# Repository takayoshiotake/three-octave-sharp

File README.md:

# Three Octave \#

[![CC BY-SA 4.0][cc-by-sa-shield]][cc-by-sa]

A 38-key (3-octave + 1) keyboard. Powered by [Vial](https://get.vial.today/) firmware.

This keyboard is based on a 60% column staggered keyboard like the HHKB, which omits the number and symbol keys to reduce the number of keys to 38.

## Layout

v0.3.0

**Layer 0**:

MEMO: I couldn't figure out how to map keys to `fn` on macOS using Vial, so I am using Karabiner-Elements, a macOS app, to modify `right_control` to `fn`.

**Layer 1, 2**: arrows, symbols

**Layer 3, 4**: nums, symbols

**Layer 5**: fn

**RAW data for Keyboard Layout Editor v0.15:**

📄 [keyboard-layout.rawdata.json](layout/keyboard-layout.rawdata.json)

```json
[{a:1},"LT 2\nEsc",{a:7},"Q","W","E","R","T","Y","U","I","O","P","Bksp"],
[{a:1,w:1.25},"LT 1\nTab",{a:7},"A","S","D","F","G","H","J","K","L",{a:1,w:1.75},"LT 4\nEnter"],
[{a:7,w:1.75},"LShift","Z","X","C","V","B","N","M","MO(5)",{w:2.25},"MO(3)"],
[{x:0.75,w:1.25},"LCtrl",{a:1,w:1.25},"LGui_T\n英数",{a:7,w:6},"6u",{a:1},"RAlt_T\nかな",{a:7},"RCtrl"],
```

- 🔗 [Keyboard Layout Editor](http://www.keyboard-layout-editor.com/)

## BOM

| Material | QTY | Note |
|-|-:|-|
| Three Octave Sharp PCBA | 1 | |
| Three Octave Sharp Case | 1 | |
| B-0204 | 4 | Screw M2 L4, Hirosugi |
| SIS-2039-05 | 4 | Washer d2 D3.9 t0.5, Hirosugi |
| LUW-0204-075 | 4 | Washer d2.2 D4 t0.075, Hirosugi |

### Three Octave Sharp PCBA

| Material | Symbol | QTY | Note |
|-|-|-:|-|
| Three Octave Sharp PCB | - | 1 | |
| 30pF 402 | C1, C2 | 2 | C1570 |
| 1uF 402 | C3, C4 | 2 | C52923 |
| 100nF 402 | C5-C14 | 10 | C307331 |
| 10uF 402 | C15, C16 | 2 | C15525 |
| HRO_TYPE-C-31-M-12 | J1 | 1 | C165948; USB Type-C Connector, Korean Hroparts Elec |
| 10KΩ 0402 | R1, R3 | 2 | C25744 |
| 1KΩ 0402 | R2, R4 | 2 | C11702 |
| 27Ω 0402 | R5, R6 | 2 | C352446 |
| 5.1KΩ 0402 | R7, R8 | 2 | C25905 |
| Hot_Swap_Socket_CPG151101S11 | SW1-SW38 | 38 | C5156480; How Swap Socket, Kailh |
| SKRPANE010 | SW_B1, SW_R1 | 2 | C470426; Tactile Switch, ALPS ALPINE |
| RP2040 | U1 | 1 | C2040; MCU, Raspberry Pi |
| W25Q64JVXGIQ | U2 | 1 | C2940195, 64M-bit Serial Flash, Winbond Electronics |
| AP2112K-3.3TRG1 | U3 | 1 | C51118, 3.3V Linear Voltage Regulators |
| X322512MSB4SI | Y1 | 1 | C9002, 12MHz 20pF Crystal Resonator, SMD-3225, Yangxing Tech |

📁 [production_data (for JLCPCB at 2024-01-25)](electronics/Three_Octave_Sharp/production/Three_Octave_Sharp_1.0.0_2024-01-25_19-34-58)

### Three Octave Sharp Case

WIP

## Schematic and PCB

📄 [Three_Octave_Sharp.kicad_sch](electronics/Three_Octave_Sharp/Three_Octave_Sharp.kicad_sch) (v1.0.0)

📄 [Three_Octave_Sharp.kicad_pcb](electronics/Three_Octave_Sharp/Three_Octave_Sharp.kicad_pcb) (v1.0.1)

### Key-matrix

|    | C0    | C1   | C2    | C3 | C4 | C5 | C6 | C7 | C8 | C9    | C10    | C11 |
|----|-------|------|-------|----|----|----|----|----|----|-------|--------|-----|
| R0 | Esc   | Q    | W     | E  | R  | T  | Y  | U  | I  | O     | P      | BS  |
| R1 | Tab   | A    | S     | D  | F  | G  | H  | J  | K  | L     | Return |     |
| R2 | Shift | Z    | X     | C  | V  | B  | N  | M  | ,  | Shift | Opt    | Fn  | 
| R3 | Ctrl  | Cmd  | Space |    |    |    |    |    |    |       |        |     |

## Mechanics

The case also functions as a plate.

- 📄 [Three-Octave-Sharp-Case.FCStd](mechanics/Three-Octave-Sharp-Case.FCStd) (v1.0.3)
    - 📄 [Three-Octave-Sharp-Case-Top.step](mechanics/Three-Octave-Sharp-Case-Top.step)
    - 📄 [Three-Octave-Sharp-Case-Bottom.step](Three-Octave-Sharp-Case-Bottom.step)

<div style="display: grid; gap: 1px; grid-template: 'a0 a0 a0 a0' 'a2t a2t a2b a2b' 'a5t a5t a5b a5b' 'a1 a3 a4 a6';">

</div>

## Firmware

### Vial

- Built UF2
    - 📄 [takayoshiotake_three_octave_sharp_vial_20240407.uf2](vial-bin/takayoshiotake_three_octave_sharp_vial_20240407.uf2)
- Code
    - 🔗 <https://github.com/vial-kb/vial-qmk/tree/vial/keyboards/takayoshiotake/three_octave_sharp>
    - 🔗 <https://github.com/vial-kb/vial-qmk/tree/bbaed80505cf4ceaeb51d1e5fe79b23b22acf1a6>

See [vial-porting](vial-porting) for more details.

## License

This work is licensed under a
[Creative Commons Attribution-ShareAlike 4.0 International License][cc-by-sa].

[![CC BY-SA 4.0][cc-by-sa-image]][cc-by-sa]

[cc-by-sa]: http://creativecommons.org/licenses/by-sa/4.0/
[cc-by-sa-image]: https://licensebuttons.net/l/by-sa/4.0/88x31.png
[cc-by-sa-shield]: https://img.shields.io/badge/license-CC%20BY--SA%204.0-lightgrey.svg

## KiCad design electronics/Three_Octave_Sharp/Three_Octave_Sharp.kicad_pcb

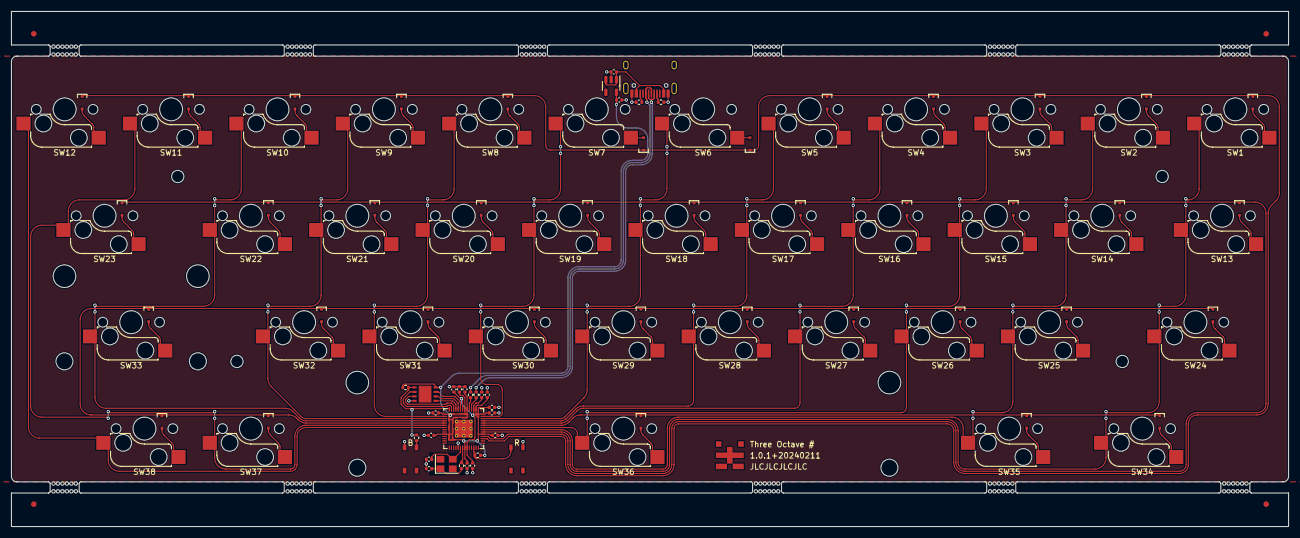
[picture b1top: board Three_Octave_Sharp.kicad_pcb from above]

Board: 2 copper layers, 228.6 x 92.2 mm, 107 parts (0 on the bottom side), 75 nets.

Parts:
C1, C2: 30pF; C_0402_1005Metric
C3, C4: 1uF; C_0402_1005Metric
C5, C6, C7, C8, C9, C10, C11, C12, C13, C14: 0.1uF; C_0402_1005Metric
C15, C16: 10uF; C_0402_1005Metric
D1, D2, D3, D4, D5, D6, D7, D8, D9, D10, D11, D12, D13, D14, D15, D16, D17, D18, D19, D20, D21, D22, D23, D24, D25, D26, D27, D28, D29, D30, D31, D32, D33, D34, D35, D36, D37, D38: 1N4148WS; D_SOD-323F
J1: HRO_TYPE-C-31-M-12
R1, R3: 10K; R_0402_1005Metric
R2, R4: 1K; R_0402_1005Metric
R5, R6: 27; R_0402_1005Metric
R7, R8: 5.1K; R_0402_1005Metric
SW1: Key Tab; Hot_Swap_Socket_CPG151101S11
SW2: Key Q; Hot_Swap_Socket_CPG151101S11
SW3: Key W; Hot_Swap_Socket_CPG151101S11
SW4: Key E; Hot_Swap_Socket_CPG151101S11
SW5: Key R; Hot_Swap_Socket_CPG151101S11
SW6: Key T; Hot_Swap_Socket_CPG151101S11
SW7: Key Y; Hot_Swap_Socket_CPG151101S11
SW8: Key U; Hot_Swap_Socket_CPG151101S11
SW9: Key I; Hot_Swap_Socket_CPG151101S11
SW10: Key O; Hot_Swap_Socket_CPG151101S11
SW11: Key P; Hot_Swap_Socket_CPG151101S11
SW12: Key BS; Hot_Swap_Socket_CPG151101S11
SW13: Key Caps; Hot_Swap_Socket_CPG151101S11
SW14: Key A; Hot_Swap_Socket_CPG151101S11
SW15: Key S; Hot_Swap_Socket_CPG151101S11
SW16: Key D; Hot_Swap_Socket_CPG151101S11
SW17: Key F; Hot_Swap_Socket_CPG151101S11
SW18: Key G; Hot_Swap_Socket_CPG151101S11
SW19: Key H; Hot_Swap_Socket_CPG151101S11
SW20: Key J; Hot_Swap_Socket_CPG151101S11
SW21: Key K; Hot_Swap_Socket_CPG151101S11
SW22: Key L; Hot_Swap_Socket_CPG151101S11
SW23: Key Return; Hot_Swap_Socket_CPG151101S11
SW24, SW33: Key Shift; Hot_Swap_Socket_CPG151101S11
SW25: Key Z; Hot_Swap_Socket_CPG151101S11
SW26: Key X; Hot_Swap_Socket_CPG151101S11
SW27: Key C; Hot_Swap_Socket_CPG151101S11
SW28: Key V; Hot_Swap_Socket_CPG151101S11
SW29: Key B; Hot_Swap_Socket_CPG151101S11
SW30: Key N; Hot_Swap_Socket_CPG151101S11
SW31: Key M; Hot_Swap_Socket_CPG151101S11
SW32: Key ,; Hot_Swap_Socket_CPG151101S11
SW34: Key Ctrl; Hot_Swap_Socket_CPG151101S11
SW35: Key Cmd; Hot_Swap_Socket_CPG151101S11
SW36: Key Space; Hot_Swap_Socket_CPG151101S11
SW37: Key Opt; Hot_Swap_Socket_CPG151101S11
SW38: Key Fn; Hot_Swap_Socket_CPG151101S11
SW_B1: Alps_Alpine_SKRP; Tactile_Switch_SKRP_Series
SW_R1: Alps_Alpine_SKRP; Tactile_Switch_SKRP_Series
U1: Raspberry_Pi_RP2040; RP2040_QFN-56
U2: W25Q64JVXGIQ; XSON-8-EP_4x4mm
U3: AP2112K-3.3; SOT-23-5
Y1: 12MHz; Crystal_SMD_3225-4Pin_3.2x2.5mm

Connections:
+1V1: C4.1, C13.1, C14.1, U1.23 (DVDD), U1.45 (VREG_VOUT), U1.50 (DVDD)
+3V3: C3.1, C5.1, C6.1, C7.1, C8.1, C9.1, C10.1, C11.1, C12.1, C16.1, R1.1, R3.1, U1.1 (IOVDD), U1.10 (IOVDD), U1.22 (IOVDD), U1.33 (IOVDD), U1.42 (IOVDD), U1.43 (ADC_AVDD), U1.44 (VREG_VIN), U1.48 (USB_VDD), U1.49 (IOVDD), U2.8 (VCC), U3.5 (VOUT)
+5V: C15.1, J1.A4/B9 (VBUS), J1.A9/B4 (VBUS), U3.1 (VIN), U3.3 (EN)
COL0: SW1.2, SW13.2, SW24.2, SW34.2, U1.34 (GPIO22)
COL1: SW2.2, SW14.2, SW25.2, SW35.2, U1.35 (GPIO23)
COL2: SW3.2, SW15.2, SW26.2, SW36.2, U1.36 (GPIO24)
COL3: SW4.2, SW16.2, SW27.2, U1.38 (GPIO26/ADC0)
COL4: SW5.2, SW17.2, SW28.2, U1.39 (GPIO27/ADC1)
COL5: SW6.2, SW18.2, SW29.2, U1.40 (GPIO28/ADC2)
COL6: SW7.2, SW19.2, SW30.2, U1.41 (GPIO29/ADC3)
COL7: SW8.2, SW20.2, SW31.2, U1.2 (GPIO0)
COL8: SW9.2, SW21.2, SW32.2, U1.3 (GPIO1)
COL9: SW10.2, SW22.2, SW33.2, U1.4 (GPIO2)
COL10: SW11.2, SW23.2, SW37.2, U1.6 (GPIO4)
COL11: SW12.2, SW38.2, U1.7 (GPIO5)
D+: R5.1, U1.47 (USB_DP)
D-: R6.1, U1.46 (USB_DM)
GND: C1.2, C2.2, C3.2, C4.2, C5.2, C6.2, C7.2, C8.2, C9.2, C10.2, C11.2, C12.2, C13.2, C14.2, C15.2, C16.2, J1.A1/B12 (GND), J1.A12/B1 (GND), R7.2, R8.2, SW_B1.3, SW_R1.1, U1.19 (TESTEN), U1.57 (GND), U2.4 (GND), U3.2 (GND)
unnamed: C2.1, R2.2, Y1.1
unnamed: D1.2 (A), SW1.1
unnamed: D2.2 (A), SW2.1
unnamed: D3.2 (A), SW3.1
unnamed: D4.2 (A), SW4.1
unnamed: D5.2 (A), SW5.1
unnamed: D6.2 (A), SW6.1
unnamed: D7.2 (A), SW7.1
unnamed: D8.2 (A), SW8.1
unnamed: D9.2 (A), SW9.1
unnamed: D10.2 (A), SW10.1
unnamed: D11.2 (A), SW11.1
unnamed: D12.2 (A), SW12.1
unnamed: D13.2 (A), SW13.1
unnamed: D14.2 (A), SW14.1
unnamed: D15.2 (A), SW15.1
unnamed: D16.2 (A), SW16.1
unnamed: D17.2 (A), SW17.1
unnamed: D18.2 (A), SW18.1
unnamed: D19.2 (A), SW19.1
unnamed: D20.2 (A), SW20.1
unnamed: D21.2 (A), SW21.1
unnamed: D22.2 (A), SW22.1
unnamed: D23.2 (A), SW23.1
unnamed: D24.2 (A), SW24.1
unnamed: D25.2 (A), SW25.1
unnamed: D26.2 (A), SW26.1
unnamed: D27.2 (A), SW27.1
unnamed: D28.2 (A), SW28.1
unnamed: D29.2 (A), SW29.1
unnamed: D30.2 (A), SW30.1
unnamed: D31.2 (A), SW31.1
unnamed: D32.2 (A), SW32.1
unnamed: D33.2 (A), SW33.1
unnamed: D34.2 (A), SW34.1
unnamed: D35.2 (A), SW35.1
unnamed: D36.2 (A), SW36.1
unnamed: D37.2 (A), SW37.1
unnamed: D38.2 (A), SW38.1
unnamed: J1.A5 (CC1), R8.1
unnamed: J1.B5 (CC2), R7.1
unnamed: J1.A6 (D+), J1.B6 (D+), R5.2
unnamed: J1.A7 (D-), J1.B7 (D-), R6.2
unnamed: R4.2, SW_B1.1
unnamed: U1.52 (QSPI_SCLK), U2.6 (CLK)
unnamed: U1.53 (QSPI_SD0), U2.5 (DI(IO0))
unnamed: U1.55 (QSPI_SD1), U2.2 (DO(IO1))
unnamed: U1.54 (QSPI_SD2), U2.3 (IO2)
unnamed: U1.51 (QSPI_SD3), U2.7 (IO3)
unnamed: R1.2, SW_R1.3, U1.26 (RUN)
unnamed: C1.1, U1.20 (XIN), Y1.3
unnamed: R2.1, U1.21 (XOUT)
QSPI_SS_N: R3.2, R4.1, U1.56 (QSPI_SS_N), U2.1 (~CS)
ROW0: D1.1 (K), D2.1 (K), D3.1 (K), D4.1 (K), D5.1 (K), D6.1 (K), D7.1 (K), D8.1 (K), D9.1 (K), D10.1 (K), D11.1 (K), D12.1 (K), U1.31 (GPIO20)
ROW1: D13.1 (K), D14.1 (K), D15.1 (K), D16.1 (K), D17.1 (K), D18.1 (K), D19.1 (K), D20.1 (K), D21.1 (K), D22.1 (K), D23.1 (K), U1.32 (GPIO21)
ROW2: D24.1 (K), D25.1 (K), D26.1 (K), D27.1 (K), D28.1 (K), D29.1 (K), D30.1 (K), D31.1 (K), D32.1 (K), D33.1 (K), D37.1 (K), D38.1 (K), U1.5 (GPIO3)
ROW3: D34.1 (K), D35.1 (K), D36.1 (K), U1.37 (GPIO25)

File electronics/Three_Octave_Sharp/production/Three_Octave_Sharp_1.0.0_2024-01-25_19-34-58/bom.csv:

Designator,Footprint,Quantity,Value,LCSC Part #
"C1, C2",0402,2,30pF,C1570
"C10, C11, C12, C13, C14, C5, C6, C7, C8, C9",0402,10,0.1uF,C307331
"C15, C16",0402,2,10uF,C15525
"C3, C4",0402,2,1uF,C52923
"D1, D10, D11, D12, D13, D14, D15, D16, D17, D18, D19, D2, D20, D21, D22, D23, D24, D25, D26, D27, D28, D29, D3, D30, D31, D32, D33, D34, D35, D36, D37, D38, D4, D5, D6, D7, D8, D9",D_SOD-323F,38,1N4148WS,C2128
J1,HRO_TYPE-C-31-M-12,1,HRO_TYPE-C-31-M-12,C165948
"R1, R3",0402,2,10K,C25744
"R2, R4",0402,2,1K,C11702
"R5, R6",0402,2,27,C25100
"R7, R8",0402,2,5.1K,C25905
SW1,Hot_Swap_Socket_CPG151101S11,1,Key Tab,C5156480
SW10,Hot_Swap_Socket_CPG151101S11,1,Key O,C5156480
SW11,Hot_Swap_Socket_CPG151101S11,1,Key P,C5156480
SW12,Hot_Swap_Socket_CPG151101S11,1,Key BS,C5156480
SW13,Hot_Swap_Socket_CPG151101S11,1,Key Caps,C5156480
SW14,Hot_Swap_Socket_CPG151101S11,1,Key A,C5156480
SW15,Hot_Swap_Socket_CPG151101S11,1,Key S,C5156480
SW16,Hot_Swap_Socket_CPG151101S11,1,Key D,C5156480
SW17,Hot_Swap_Socket_CPG151101S11,1,Key F,C5156480
SW18,Hot_Swap_Socket_CPG151101S11,1,Key G,C5156480
SW19,Hot_Swap_Socket_CPG151101S11,1,Key H,C5156480
SW2,Hot_Swap_Socket_CPG151101S11,1,Key Q,C5156480
SW20,Hot_Swap_Socket_CPG151101S11,1,Key J,C5156480
SW21,Hot_Swap_Socket_CPG151101S11,1,Key K,C5156480
SW22,Hot_Swap_Socket_CPG151101S11,1,Key L,C5156480
SW23,Hot_Swap_Socket_CPG151101S11,1,Key Return,C5156480
"SW24, SW33",Hot_Swap_Socket_CPG151101S11,2,Key Shift,C5156480
SW25,Hot_Swap_Socket_CPG151101S11,1,Key Z,C5156480
SW26,Hot_Swap_Socket_CPG151101S11,1,Key X,C5156480
SW27,Hot_Swap_Socket_CPG151101S11,1,Key C,C5156480
SW28,Hot_Swap_Socket_CPG151101S11,1,Key V,C5156480
SW29,Hot_Swap_Socket_CPG151101S11,1,Key B,C5156480
SW3,Hot_Swap_Socket_CPG151101S11,1,Key W,C5156480
SW30,Hot_Swap_Socket_CPG151101S11,1,Key N,C5156480
SW31,Hot_Swap_Socket_CPG151101S11,1,Key M,C5156480
SW32,Hot_Swap_Socket_CPG151101S11,1,"Key ,",C5156480
SW34,Hot_Swap_Socket_CPG151101S11,1,Key Ctrl,C5156480
SW35,Hot_Swap_Socket_CPG151101S11,1,Key Cmd,C5156480
SW36,Hot_Swap_Socket_CPG151101S11,1,Key Space,C5156480
SW37,Hot_Swap_Socket_CPG151101S11,1,Key Opt,C5156480
SW38,Hot_Swap_Socket_CPG151101S11,1,Key Fn,C5156480
SW4,Hot_Swap_Socket_CPG151101S11,1,Key E,C5156480
SW5,Hot_Swap_Socket_CPG151101S11,1,Key R,C5156480
SW6,Hot_Swap_Socket_CPG151101S11,1,Key T,C5156480
SW7,Hot_Swap_Socket_CPG151101S11,1,Key Y,C5156480
SW8,Hot_Swap_Socket_CPG151101S11,1,Key U,C5156480
SW9,Hot_Swap_Socket_CPG151101S11,1,Key I,C5156480
"SW_B1, SW_R1",Tactile_Switch_SKRP_Series,2,Alps_Alpine_SKRP,C470426
U1,RP2040_QFN-56,1,Raspberry_Pi_RP2040,C2040
U2,XSON-8-EP_4x4mm,1,W25Q64JVXGIQ,C2940195
U3,SOT-23-5,1,AP2112K-3.3,C51118
Y1,Crystal_SMD_3225-4Pin_3.2x2.5mm,1,12MHz,C9002

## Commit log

2024-01-05 Add layer 0 layout
2024-01-06 Add KiCad project copied from Five Octave
    Rename it to "Three Octave #" and add the 6u stabilizer footprint
2024-01-07 Remove meaningless wire
2024-01-07 Add schematic and PCB design copied from Five Octave
2024-01-07 Layout keys on PCB
2024-01-07 WIP: Update schematic and PCB design
2024-01-09 Change layout to slightly
2024-01-09 WIP: Update PCB design
2024-01-16 Change paper size
2024-01-19 Add 3D shape for USB-C connector
2024-01-20 Change PCB thickness to 1.2 mm
2024-01-20 Fix stabilizer-2u footprint
2024-01-20 Fix stabilizer footprint (2u, 6u)
2024-01-20 WIP: Add case design
2024-01-22 WIP: Update case design
2024-01-24 WIP: Update 3d design
2024-01-25 Change resistor part # for JLCPCB
2024-01-25 Add edge rails and fiducials
2024-01-25 Rename
2024-01-25 Update PCB version number
2024-01-26 Add production files
2024-02-10 Add vial firmware
2024-02-11 Fix pcb outline (0.005 mm)
2024-02-11 V up
2024-02-11 Fix case-bottom for reset and boot switches
2024-02-11 Improve connectors for edge rails
2024-02-27 Modify case-bottom for CNC
2024-03-05 Modify default keymap
2024-03-05 Fix link to fw
2024-03-05 Modify case-bottom logo
2024-03-06 Create LICENSE
2024-04-06 Fix keyboard UID, and change layer count
2024-04-06 Update FW
2024-04-07 Change default keymap
2024-04-07 Format code
2024-05-14 Add each layer images
2024-06-02 Add key-matrix
2024-06-08 Add BOM (WIP)
2024-06-09 Add case images
2024-06-09 Reorder case images
    Improve when grid styles are disabled
2024-06-09 Add explanation of keyboard concepts
